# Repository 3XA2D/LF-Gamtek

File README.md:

# LF-Gamtek
## Analog Line Follower Robot
This project is made for the purpose of completing the Technical Drawing Workshop
The end goal for this project is to have a complete analog line follower robot schematic, simulation, and PCB design

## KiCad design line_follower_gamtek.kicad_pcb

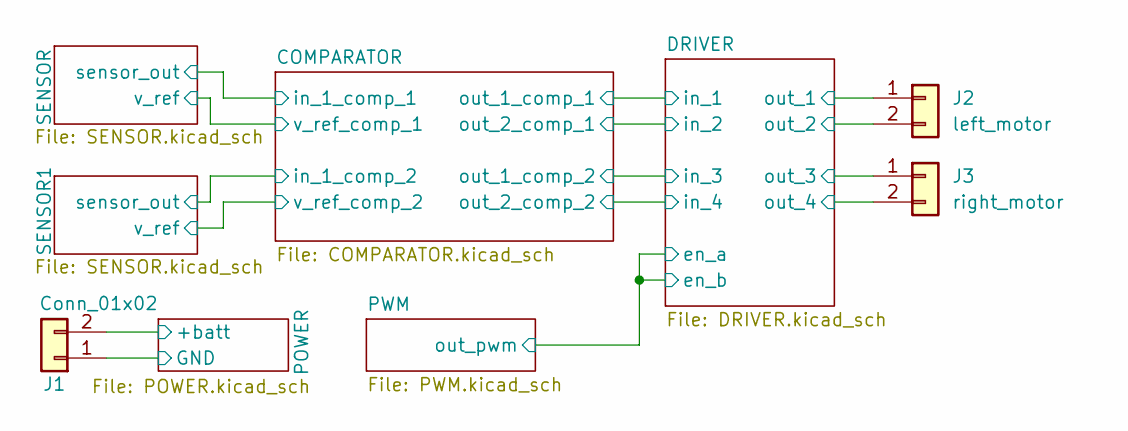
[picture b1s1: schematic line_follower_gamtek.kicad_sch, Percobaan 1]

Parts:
J1: Conn_01x02; TerminalBlock_Phoenix_MKDS-1,5-2-5.08_1x02_P5.08mm_Horizont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
J2: left_motor; TerminalBlock_Phoenix_MKDS-1,5-2-5.08_1x02_P5.08mm_Horizont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
J3: right_motor; TerminalBlock_Phoenix_MKDS-1,5-2-5.08_1x02_P5.08mm_Horizont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

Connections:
/DRIVER/out_1: J2.1; also elsewhere on the board
/DRIVER/out_2: J2.2; also elsewhere on the board
/DRIVER/out_3: J3.1; also elsewhere on the board
/DRIVER/out_4: J3.2; also elsewhere on the board
/POWER/+batt: J1.2; also elsewhere on the board
GND: J1.1; also elsewhere on the board

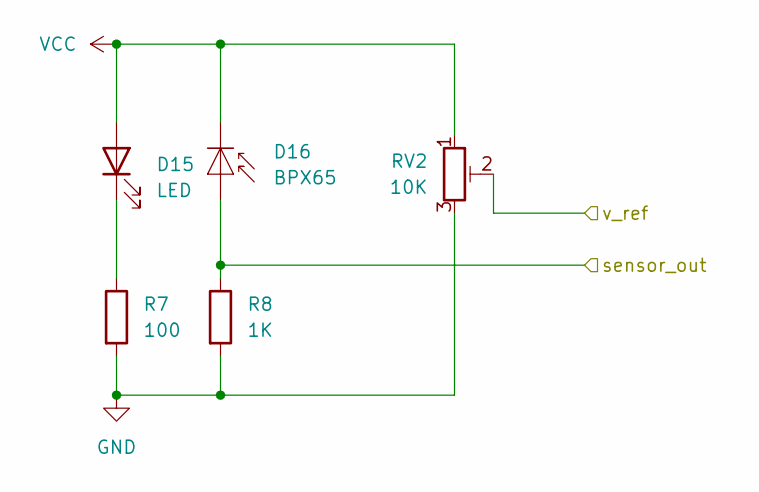
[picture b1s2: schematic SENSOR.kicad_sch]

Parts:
D15: LED; LED_D5.0mm
D16: BPX65; LED_D5.0mm
R7: 100; R_Axial_DIN0207_L6.3mm_D2.5mm_P7.62mm_Horizontal
R8: 1K; R_Axial_DIN0207_L6.3mm_D2.5mm_P7.62mm_Horizontal
RV2: 10K; Potentiometer_Bourns_3296W_Vertical

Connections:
/COMPARATOR/in_1_comp_1: D16.2 (A), R8.1; also elsewhere on the board
/COMPARATOR/v_ref_comp_1: RV2.2; also elsewhere on the board
GND: R7.2, R8.2, RV2.3; also elsewhere on the board
unnamed: D15.1 (K), R7.1
VCC: D15.2 (A), D16.1 (K), RV2.1; also elsewhere on the board

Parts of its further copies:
D4: LED; LED_D5.0mm
D5: BPX65; LED_D5.0mm
R4: 100; R_Axial_DIN0207_L6.3mm_D2.5mm_P7.62mm_Horizontal
R5: 1K; R_Axial_DIN0207_L6.3mm_D2.5mm_P7.62mm_Horizontal
RV3: 10K; Potentiometer_Bourns_3296W_Vertical

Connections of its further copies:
/COMPARATOR/in_1_comp_2: D5.2 (A), R5.1; also elsewhere on the board
/COMPARATOR/v_ref_comp_2: RV3.2; also elsewhere on the board
GND: R4.2, R5.2, RV3.3; also elsewhere on the board
unnamed: D4.1 (K), R4.1
VCC: D4.2 (A), D5.1 (K), RV3.1; also elsewhere on the board

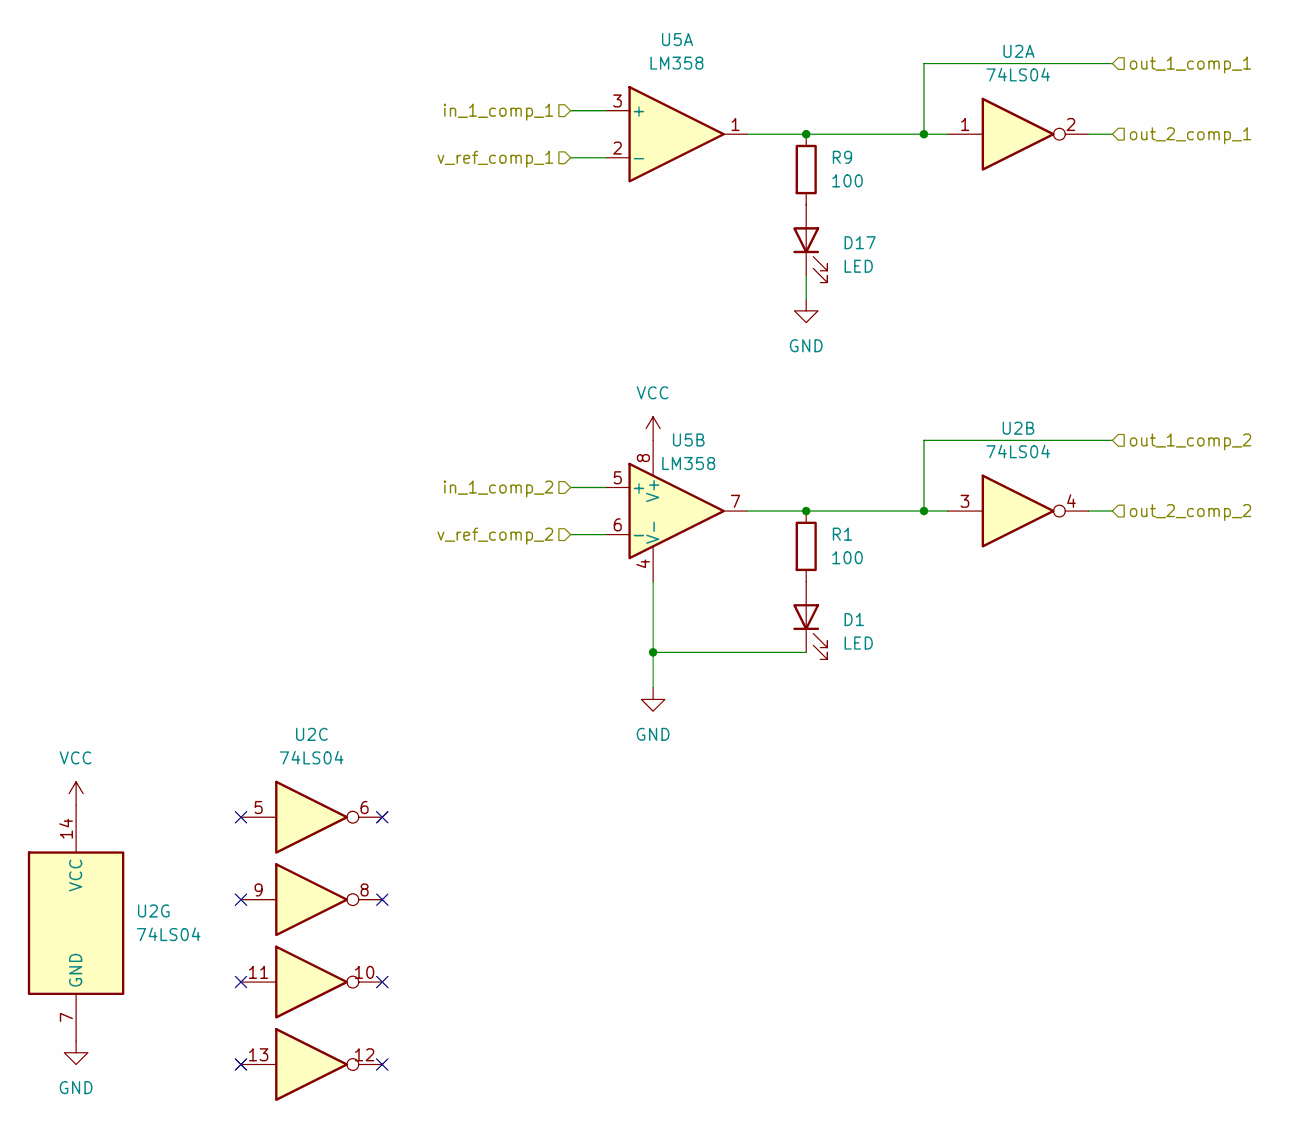
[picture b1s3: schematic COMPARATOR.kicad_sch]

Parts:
D1, D17: LED; LED_D5.0mm
R1, R9: 100; R_Axial_DIN0207_L6.3mm_D2.5mm_P7.62mm_Horizontal
U2: 74LS04; DIP-14_W7.62mm
U5: LM358; DIP-8_W7.62mm

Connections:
/COMPARATOR/in_1_comp_1: U5.3 (+); also elsewhere on the board
/COMPARATOR/in_1_comp_2: U5.5 (+); also elsewhere on the board
/COMPARATOR/out_1_comp_1: R9.1, U2.1, U5.1; also elsewhere on the board
/COMPARATOR/out_1_comp_2: R1.1, U2.3, U5.7; also elsewhere on the board
/COMPARATOR/out_2_comp_1: U2.2; also elsewhere on the board
/COMPARATOR/out_2_comp_2: U2.4; also elsewhere on the board
/COMPARATOR/v_ref_comp_1: U5.2 (-); also elsewhere on the board
/COMPARATOR/v_ref_comp_2: U5.6 (-); also elsewhere on the board
GND: D1.1 (K), D17.1 (K), U2.7 (GND), U5.4 (V-); also elsewhere on the board
unnamed: D1.2 (A), R1.2
unnamed: D17.2 (A), R9.2
VCC: U2.14 (VCC), U5.8 (V+); also elsewhere on the board

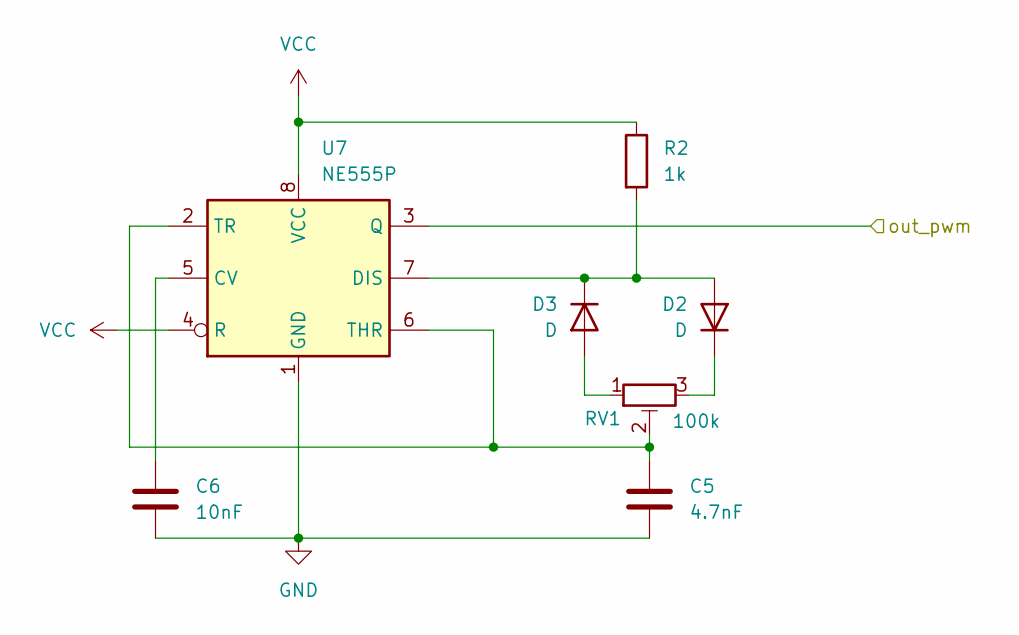
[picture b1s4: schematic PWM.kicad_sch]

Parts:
C5: 4.7nF; C_Disc_D5.0mm_W2.5mm_P5.00mm
C6: 10nF; C_Disc_D5.0mm_W2.5mm_P5.00mm
D2, D3: D; D_DO-35_SOD27_P7.62mm_Horizontal
R2: 1k; R_Axial_DIN0207_L6.3mm_D2.5mm_P7.62mm_Horizontal
RV1: 100k; Potentiometer_Bourns_3296W_Vertical
U7: NE555P; DIP-8_W7.62mm

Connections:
/DRIVER/en_a: U7.3 (Q); also elsewhere on the board
GND: C5.2, C6.2, U7.1 (GND); also elsewhere on the board
unnamed: D2.2 (A), D3.1 (K), R2.2, U7.7 (DIS)
unnamed: D2.1 (K), RV1.3
unnamed: D3.2 (A), RV1.1
unnamed: C6.1, U7.5 (CV)
unnamed: C5.1, RV1.2, U7.2 (TR), U7.6 (THR)
VCC: R2.1, U7.4 (R), U7.8 (VCC); also elsewhere on the board

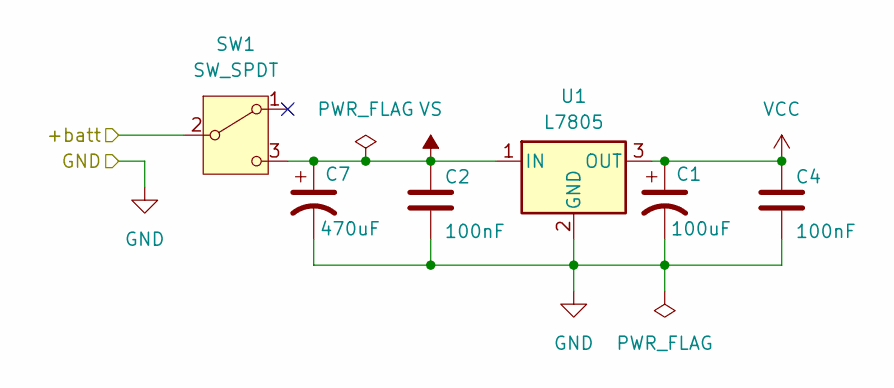
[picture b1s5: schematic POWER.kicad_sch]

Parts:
C1: 100uF; CP_Radial_D6.3mm_P2.50mm
C2, C4: 100nF; C_Disc_D5.0mm_W2.5mm_P5.00mm
C7: 470uF; CP_Radial_D10.0mm_P5.00mm
SW1: SW_SPDT; SW_Slide_SPDT_Straight_CK_OS102011MS2Q
U1: L7805; TO-220-3_Vertical

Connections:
/POWER/+batt: SW1.2 (B); also elsewhere on the board
GND: C1.2, C2.2, C4.2, C7.2, U1.2 (GND); also elsewhere on the board
VCC: C1.1, C4.1, U1.3 (OUT); also elsewhere on the board
VS: C2.1, C7.1, SW1.3 (C), U1.1 (IN); also elsewhere on the board

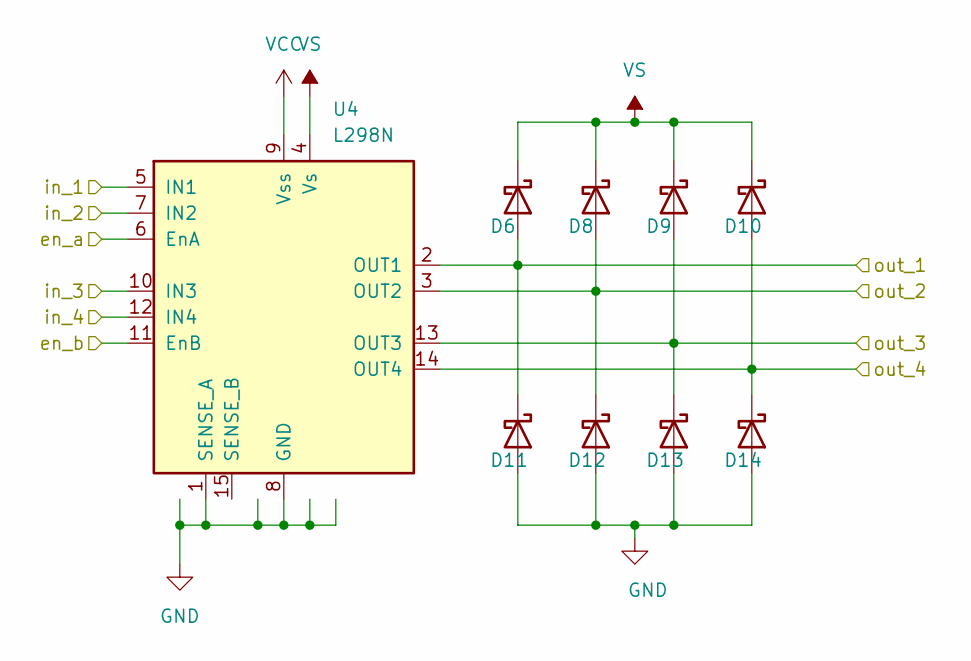
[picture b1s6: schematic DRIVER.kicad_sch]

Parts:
D6, D8, D9, D10, D11, D12, D13, D14: D_Schottky; D_DO-41_SOD81_P10.16mm_Horizontal
U4: L298N; TO-220-15_P2.54x5.08mm_StaggerOdd_Lead4.58mm_Vertical

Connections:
/COMPARATOR/out_1_comp_1: U4.5 (IN1); also elsewhere on the board
/COMPARATOR/out_1_comp_2: U4.10 (IN3); also elsewhere on the board
/COMPARATOR/out_2_comp_1: U4.7 (IN2); also elsewhere on the board
/COMPARATOR/out_2_comp_2: U4.12 (IN4); also elsewhere on the board
/DRIVER/en_a: U4.6 (EnA), U4.11 (EnB); also elsewhere on the board
/DRIVER/out_1: D6.2 (A), D11.1 (K), U4.2 (OUT1); also elsewhere on the board
/DRIVER/out_2: D8.2 (A), D12.1 (K), U4.3 (OUT2); also elsewhere on the board
/DRIVER/out_3: D9.2 (A), D13.1 (K), U4.13 (OUT3); also elsewhere on the board
/DRIVER/out_4: D10.2 (A), D14.1 (K), U4.14 (OUT4); also elsewhere on the board
GND: D11.2 (A), D12.2 (A), D13.2 (A), D14.2 (A), U4.1 (SENSE_A), U4.8 (GND); also elsewhere on the board
VCC: U4.9 (Vss); also elsewhere on the board
VS: D6.1 (K), D8.1 (K), D9.1 (K), D10.1 (K), U4.4 (Vs); also elsewhere on the board

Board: 2 copper layers, 41 parts (0 on the bottom side), 26 nets, no tracks yet.
